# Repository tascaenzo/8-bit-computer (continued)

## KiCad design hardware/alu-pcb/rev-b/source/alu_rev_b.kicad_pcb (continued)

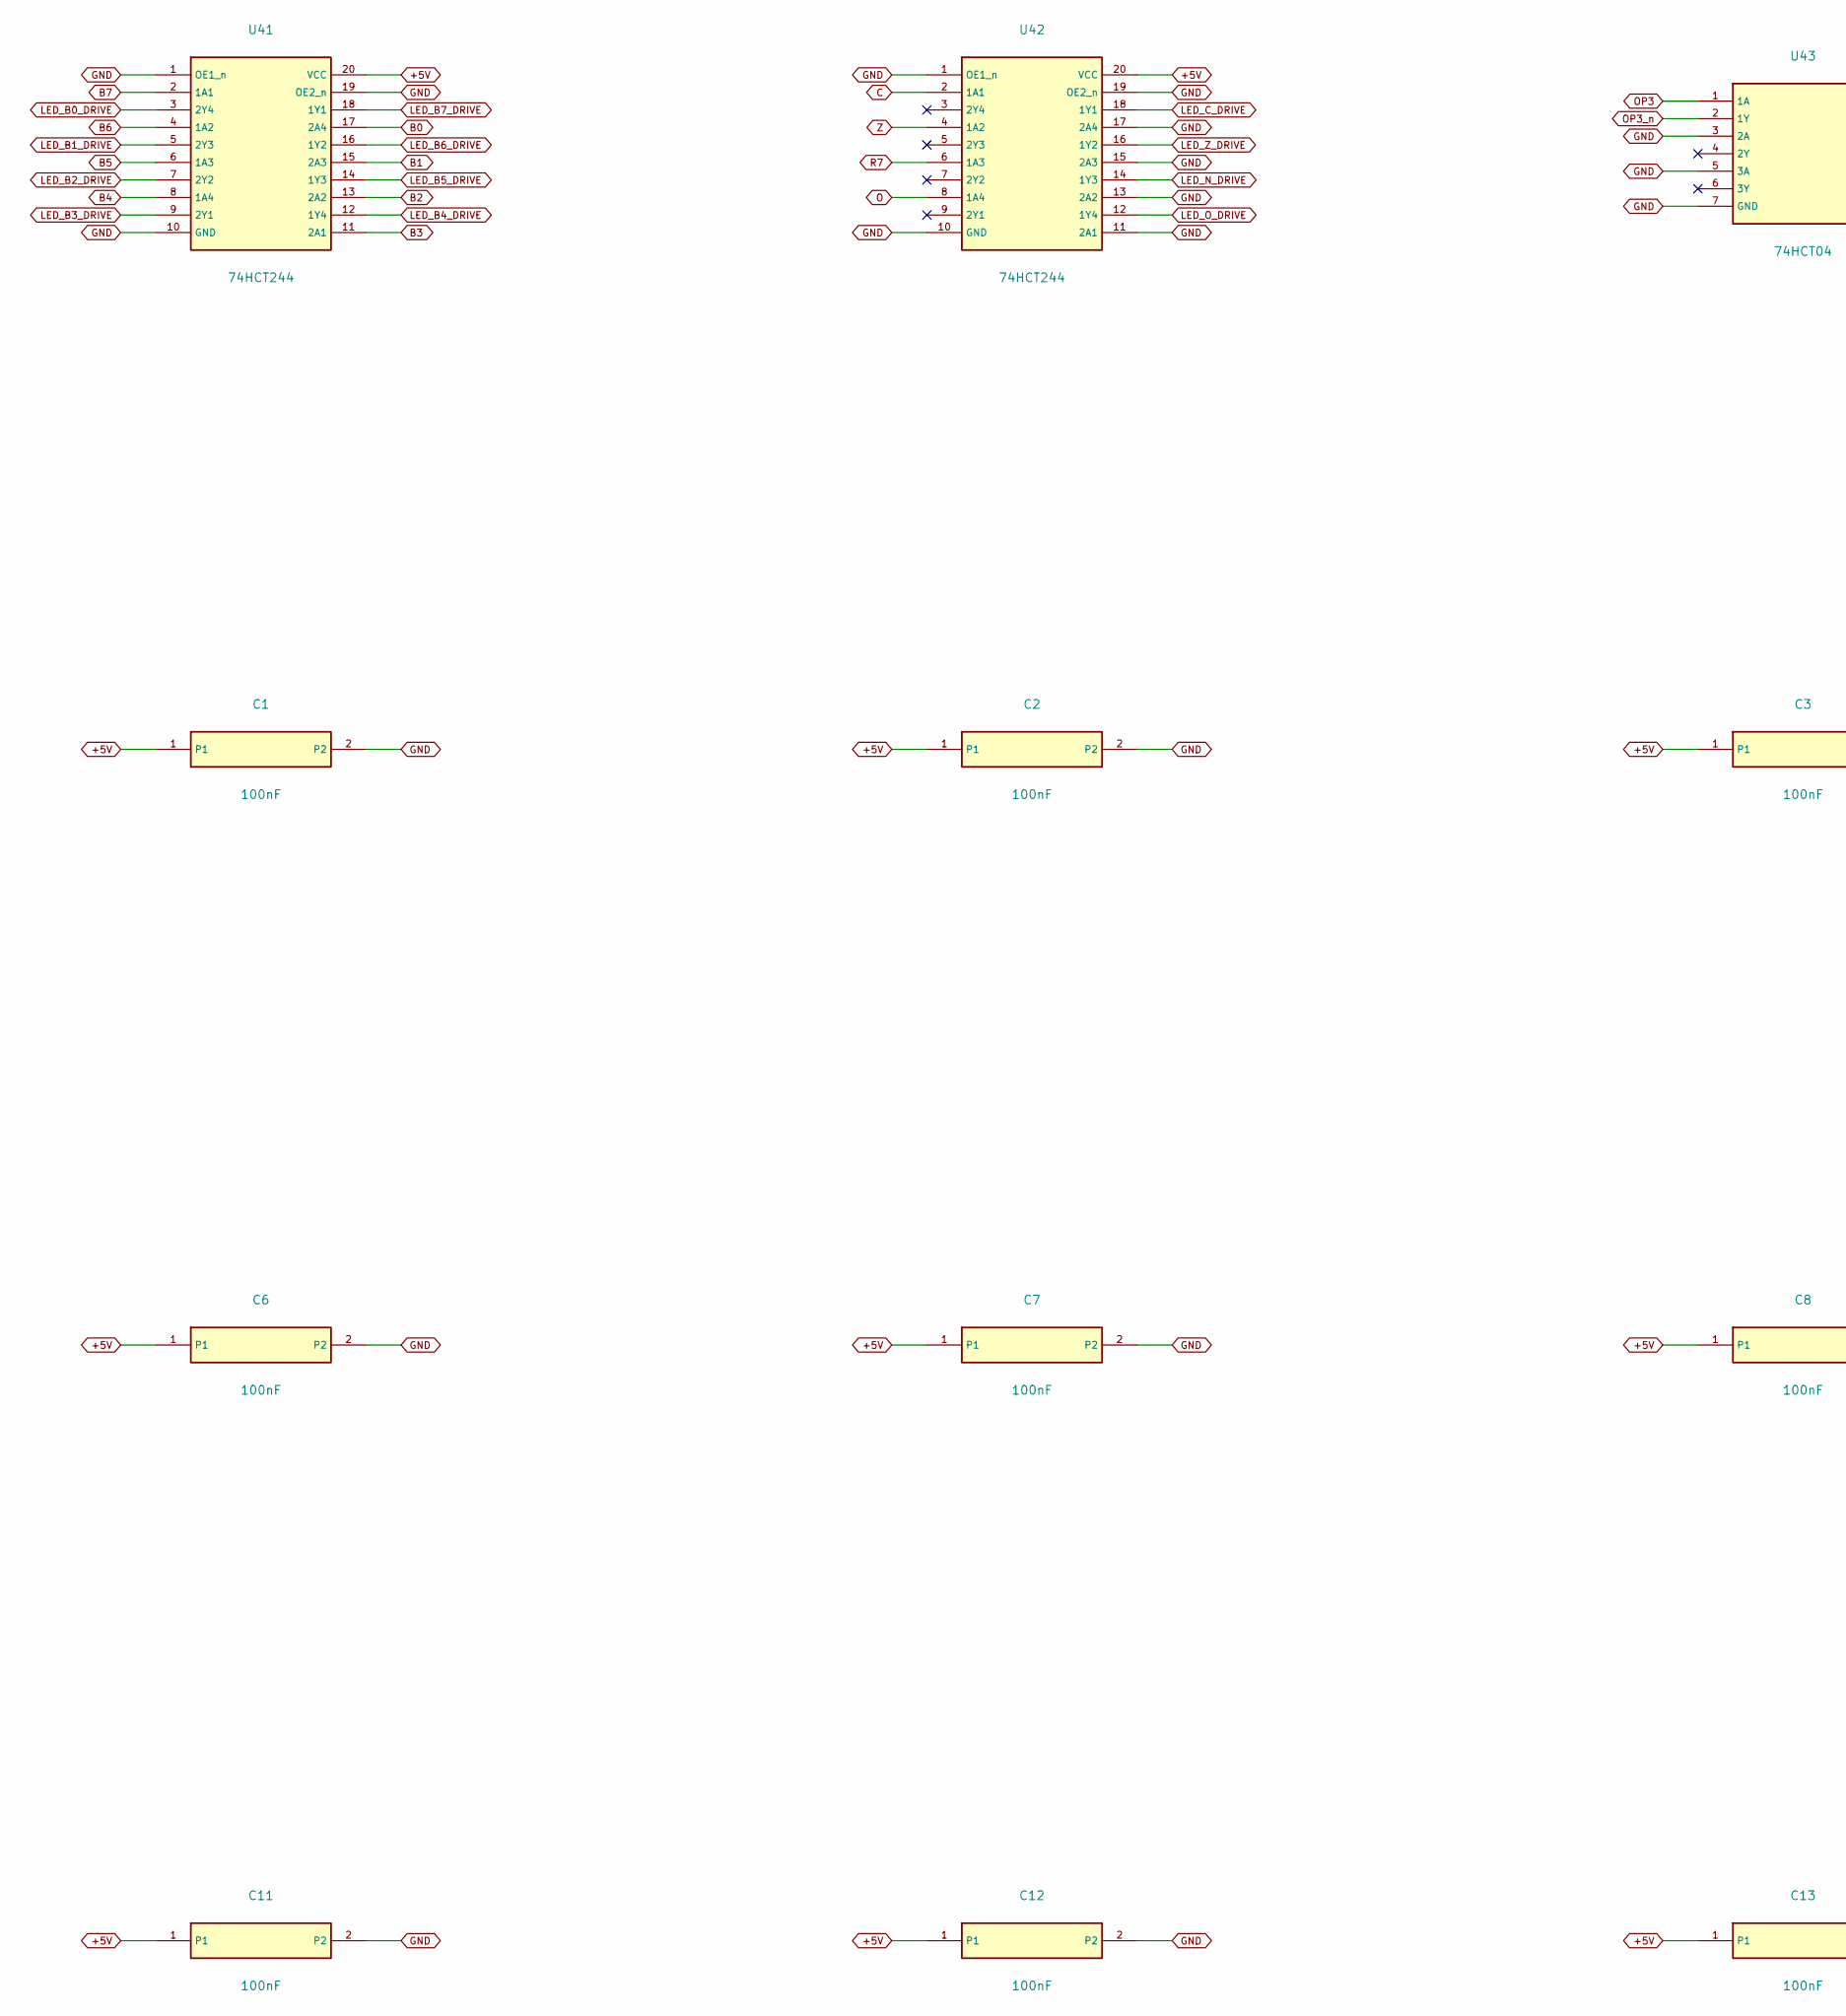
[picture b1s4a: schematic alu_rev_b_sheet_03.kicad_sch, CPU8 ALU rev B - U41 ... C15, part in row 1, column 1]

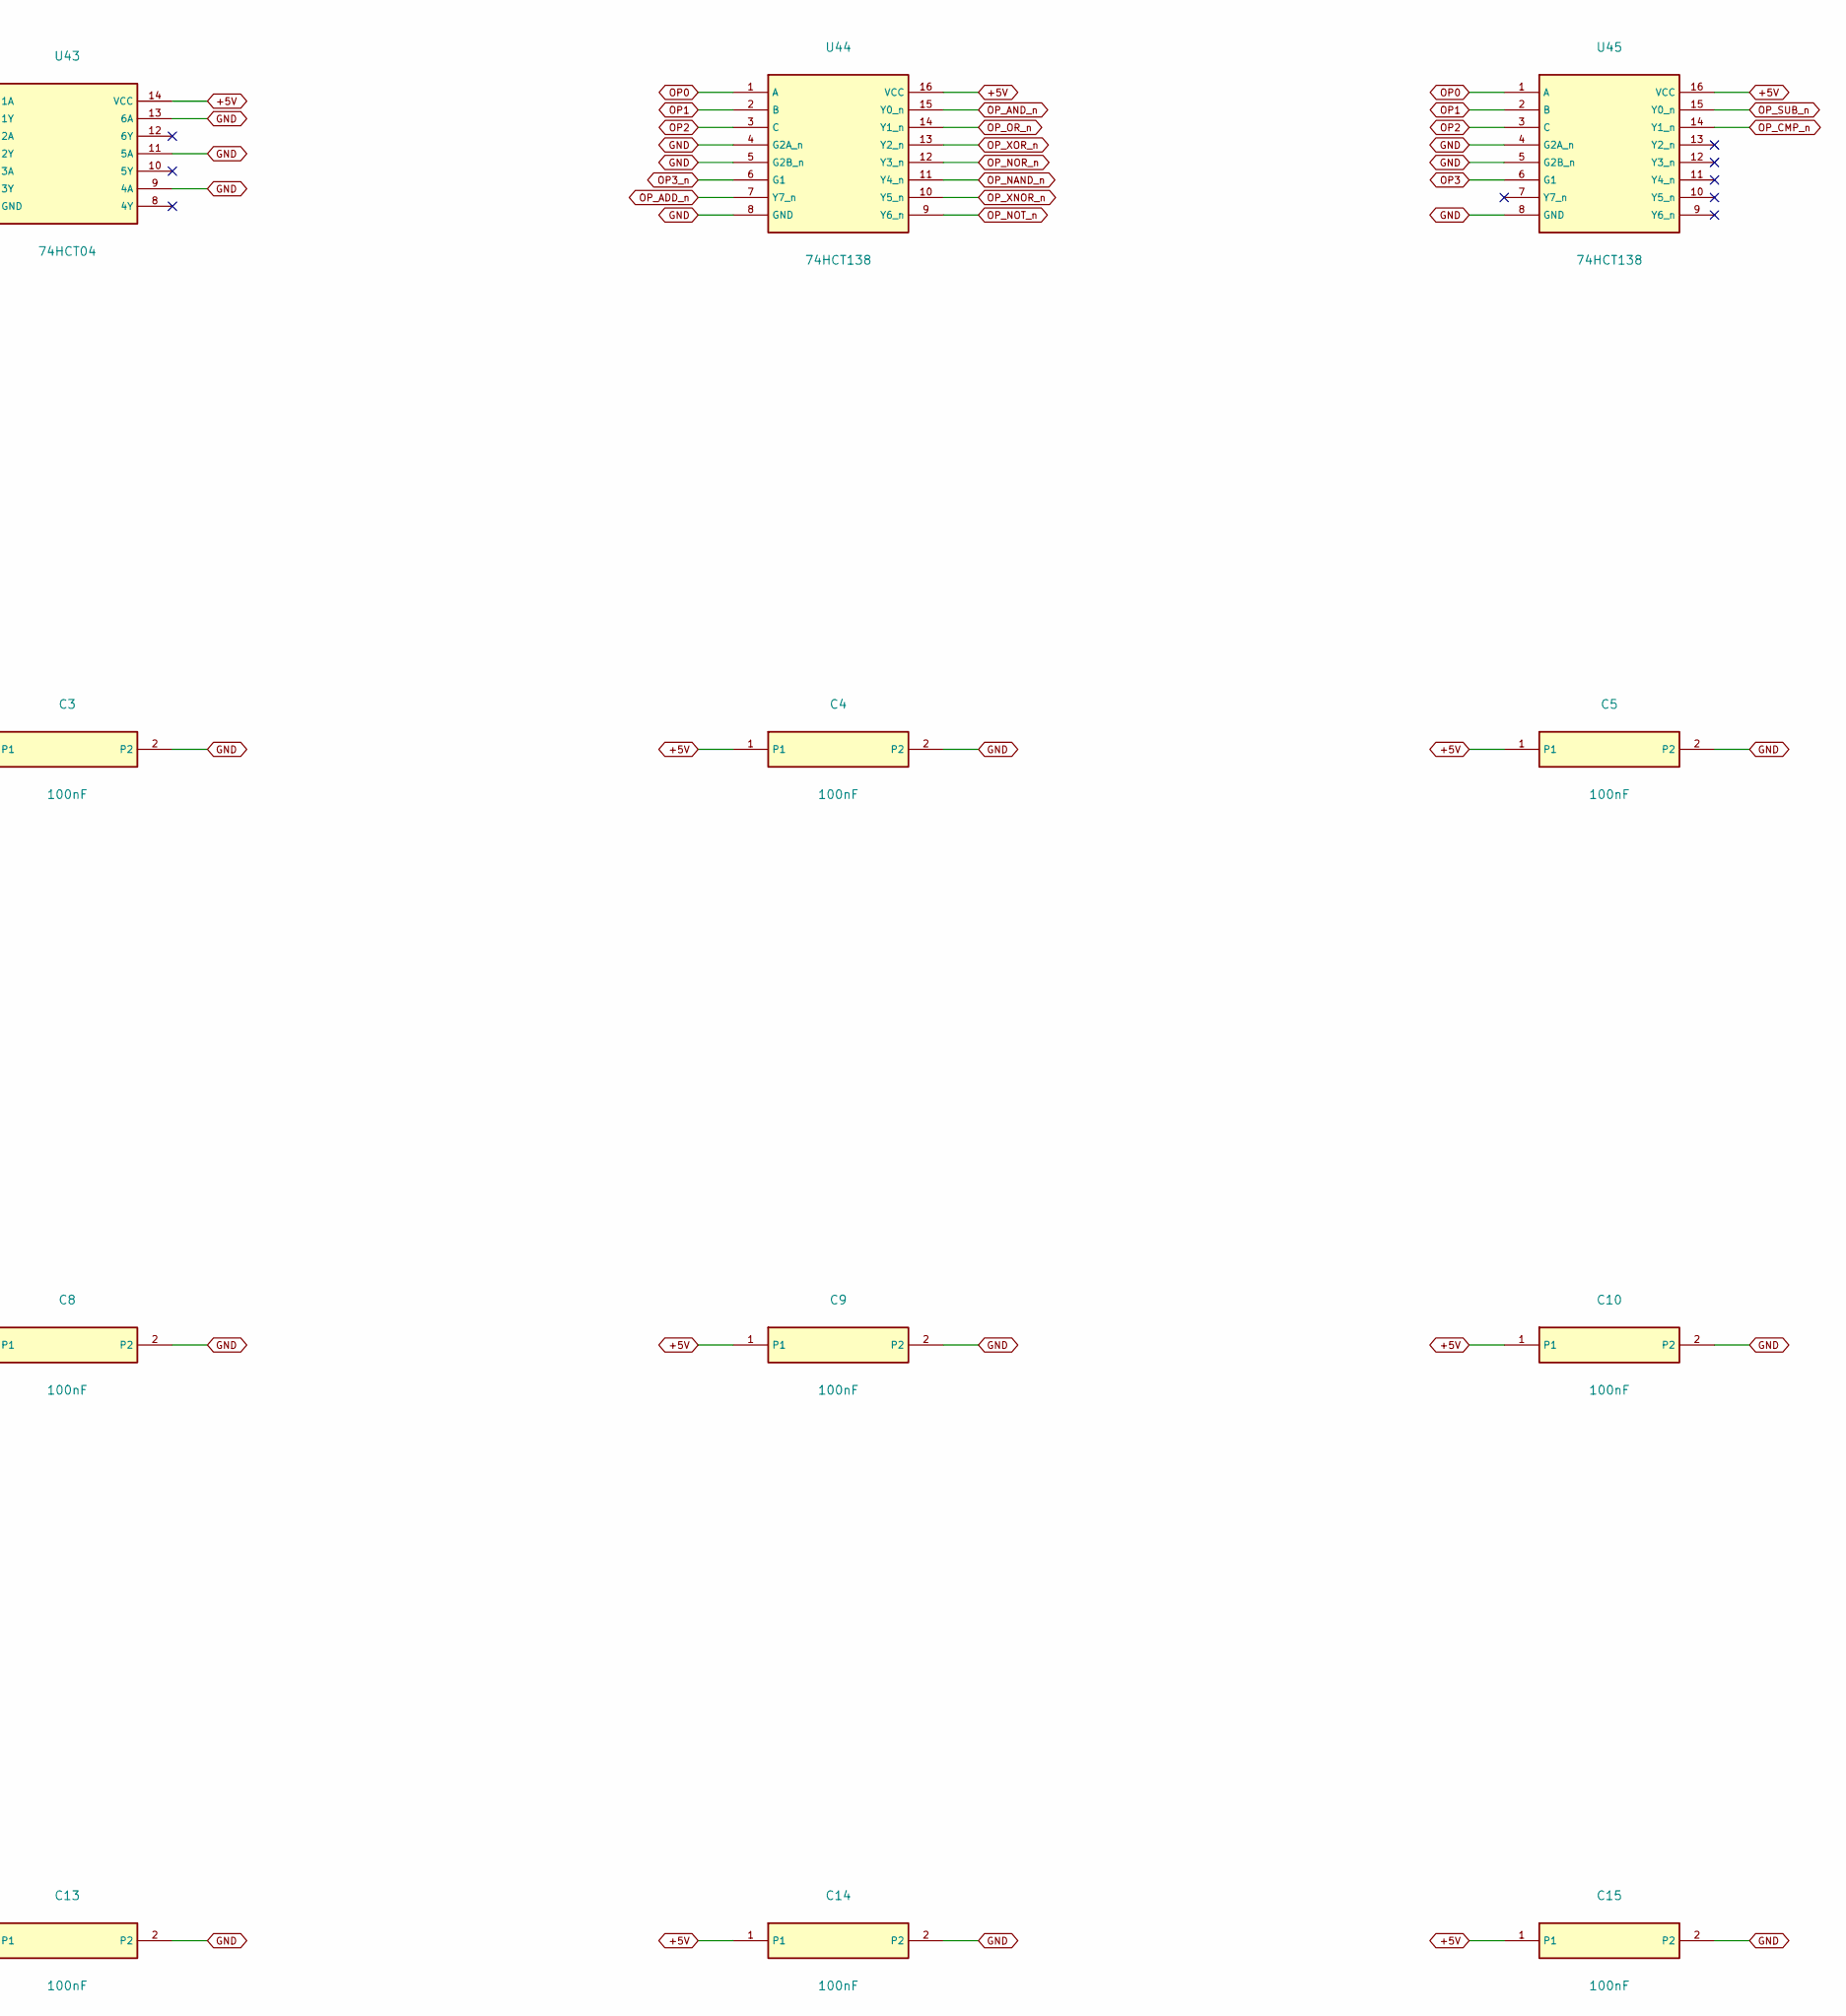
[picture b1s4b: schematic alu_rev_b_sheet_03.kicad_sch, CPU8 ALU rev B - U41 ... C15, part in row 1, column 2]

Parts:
C1, C2, C3, C4, C5, C6, C7, C8, C9, C10, C11, C12, C13, C14, C15: 100nF; C_Disc_P2.50mm
U41, U42: 74HCT244; DIP-20_W7.62mm
U43: 74HCT04; DIP-14_W7.62mm
U44, U45: 74HCT138; DIP-16_W7.62mm

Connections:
+5V: C1.1, C2.1, C3.1, C4.1, C5.1, C6.1, C7.1, C8.1, C9.1, C10.1, C11.1, C12.1, C13.1, C14.1, C15.1, U41.20 (VCC), U42.20 (VCC), U43.14 (VCC), U44.16 (VCC), U45.16 (VCC); also elsewhere on the board
B0: U41.17 (2A4); also elsewhere on the board
B1: U41.15 (2A3); also elsewhere on the board
B2: U41.13 (2A2); also elsewhere on the board
B3: U41.11 (2A1); also elsewhere on the board
B4: U41.8 (1A4); also elsewhere on the board
B5: U41.6 (1A3); also elsewhere on the board
B6: U41.4 (1A2); also elsewhere on the board
B7: U41.2 (1A1); also elsewhere on the board
C: U42.2 (1A1); also elsewhere on the board
GND: C1.2, C2.2, C3.2, C4.2, C5.2, C6.2, C7.2, C8.2, C9.2, C10.2, C11.2, C12.2, C13.2, C14.2, C15.2, U41.1 (OE1_n), U41.10 (GND), U41.19 (OE2_n), U42.1 (OE1_n), U42.10 (GND), U42.11 (2A1), U42.13 (2A2), U42.15 (2A3), U42.17 (2A4), U42.19 (OE2_n), U43.3 (2A), U43.5 (3A), U43.7 (GND), U43.9 (4A), U43.11 (5A), U43.13 (6A), U44.4 (G2A_n), U44.5 (G2B_n), U44.8 (GND), U45.4 (G2A_n), U45.5 (G2B_n), U45.8 (GND); also elsewhere on the board
LED_B0_DRIVE: U41.3 (2Y4); also elsewhere on the board
LED_B1_DRIVE: U41.5 (2Y3); also elsewhere on the board
LED_B2_DRIVE: U41.7 (2Y2); also elsewhere on the board
LED_B3_DRIVE: U41.9 (2Y1); also elsewhere on the board
LED_B4_DRIVE: U41.12 (1Y4); also elsewhere on the board
LED_B5_DRIVE: U41.14 (1Y3); also elsewhere on the board
LED_B6_DRIVE: U41.16 (1Y2); also elsewhere on the board
LED_B7_DRIVE: U41.18 (1Y1); also elsewhere on the board
LED_C_DRIVE: U42.18 (1Y1); also elsewhere on the board
LED_N_DRIVE: U42.14 (1Y3); also elsewhere on the board
LED_O_DRIVE: U42.12 (1Y4); also elsewhere on the board
LED_Z_DRIVE: U42.16 (1Y2); also elsewhere on the board
O: U42.8 (1A4); also elsewhere on the board
OP0: U44.1 (A), U45.1 (A); also elsewhere on the board
OP1: U44.2 (B), U45.2 (B); also elsewhere on the board
OP2: U44.3 (C), U45.3 (C); also elsewhere on the board
OP3: U43.1 (1A), U45.6 (G1); also elsewhere on the board
OP3_n: U43.2 (1Y), U44.6 (G1)
OP_ADD_n: U44.7 (Y7_n); also elsewhere on the board
OP_AND_n: U44.15 (Y0_n); also elsewhere on the board
OP_CMP_n: U45.14 (Y1_n); also elsewhere on the board
OP_NAND_n: U44.11 (Y4_n); also elsewhere on the board
OP_NOR_n: U44.12 (Y3_n); also elsewhere on the board
OP_NOT_n: U44.9 (Y6_n); also elsewhere on the board
OP_OR_n: U44.14 (Y1_n); also elsewhere on the board
OP_SUB_n: U45.15 (Y0_n); also elsewhere on the board
OP_XNOR_n: U44.10 (Y5_n); also elsewhere on the board
OP_XOR_n: U44.13 (Y2_n); also elsewhere on the board
R7: U42.6 (1A3); also elsewhere on the board
Z: U42.4 (1A2); also elsewhere on the board

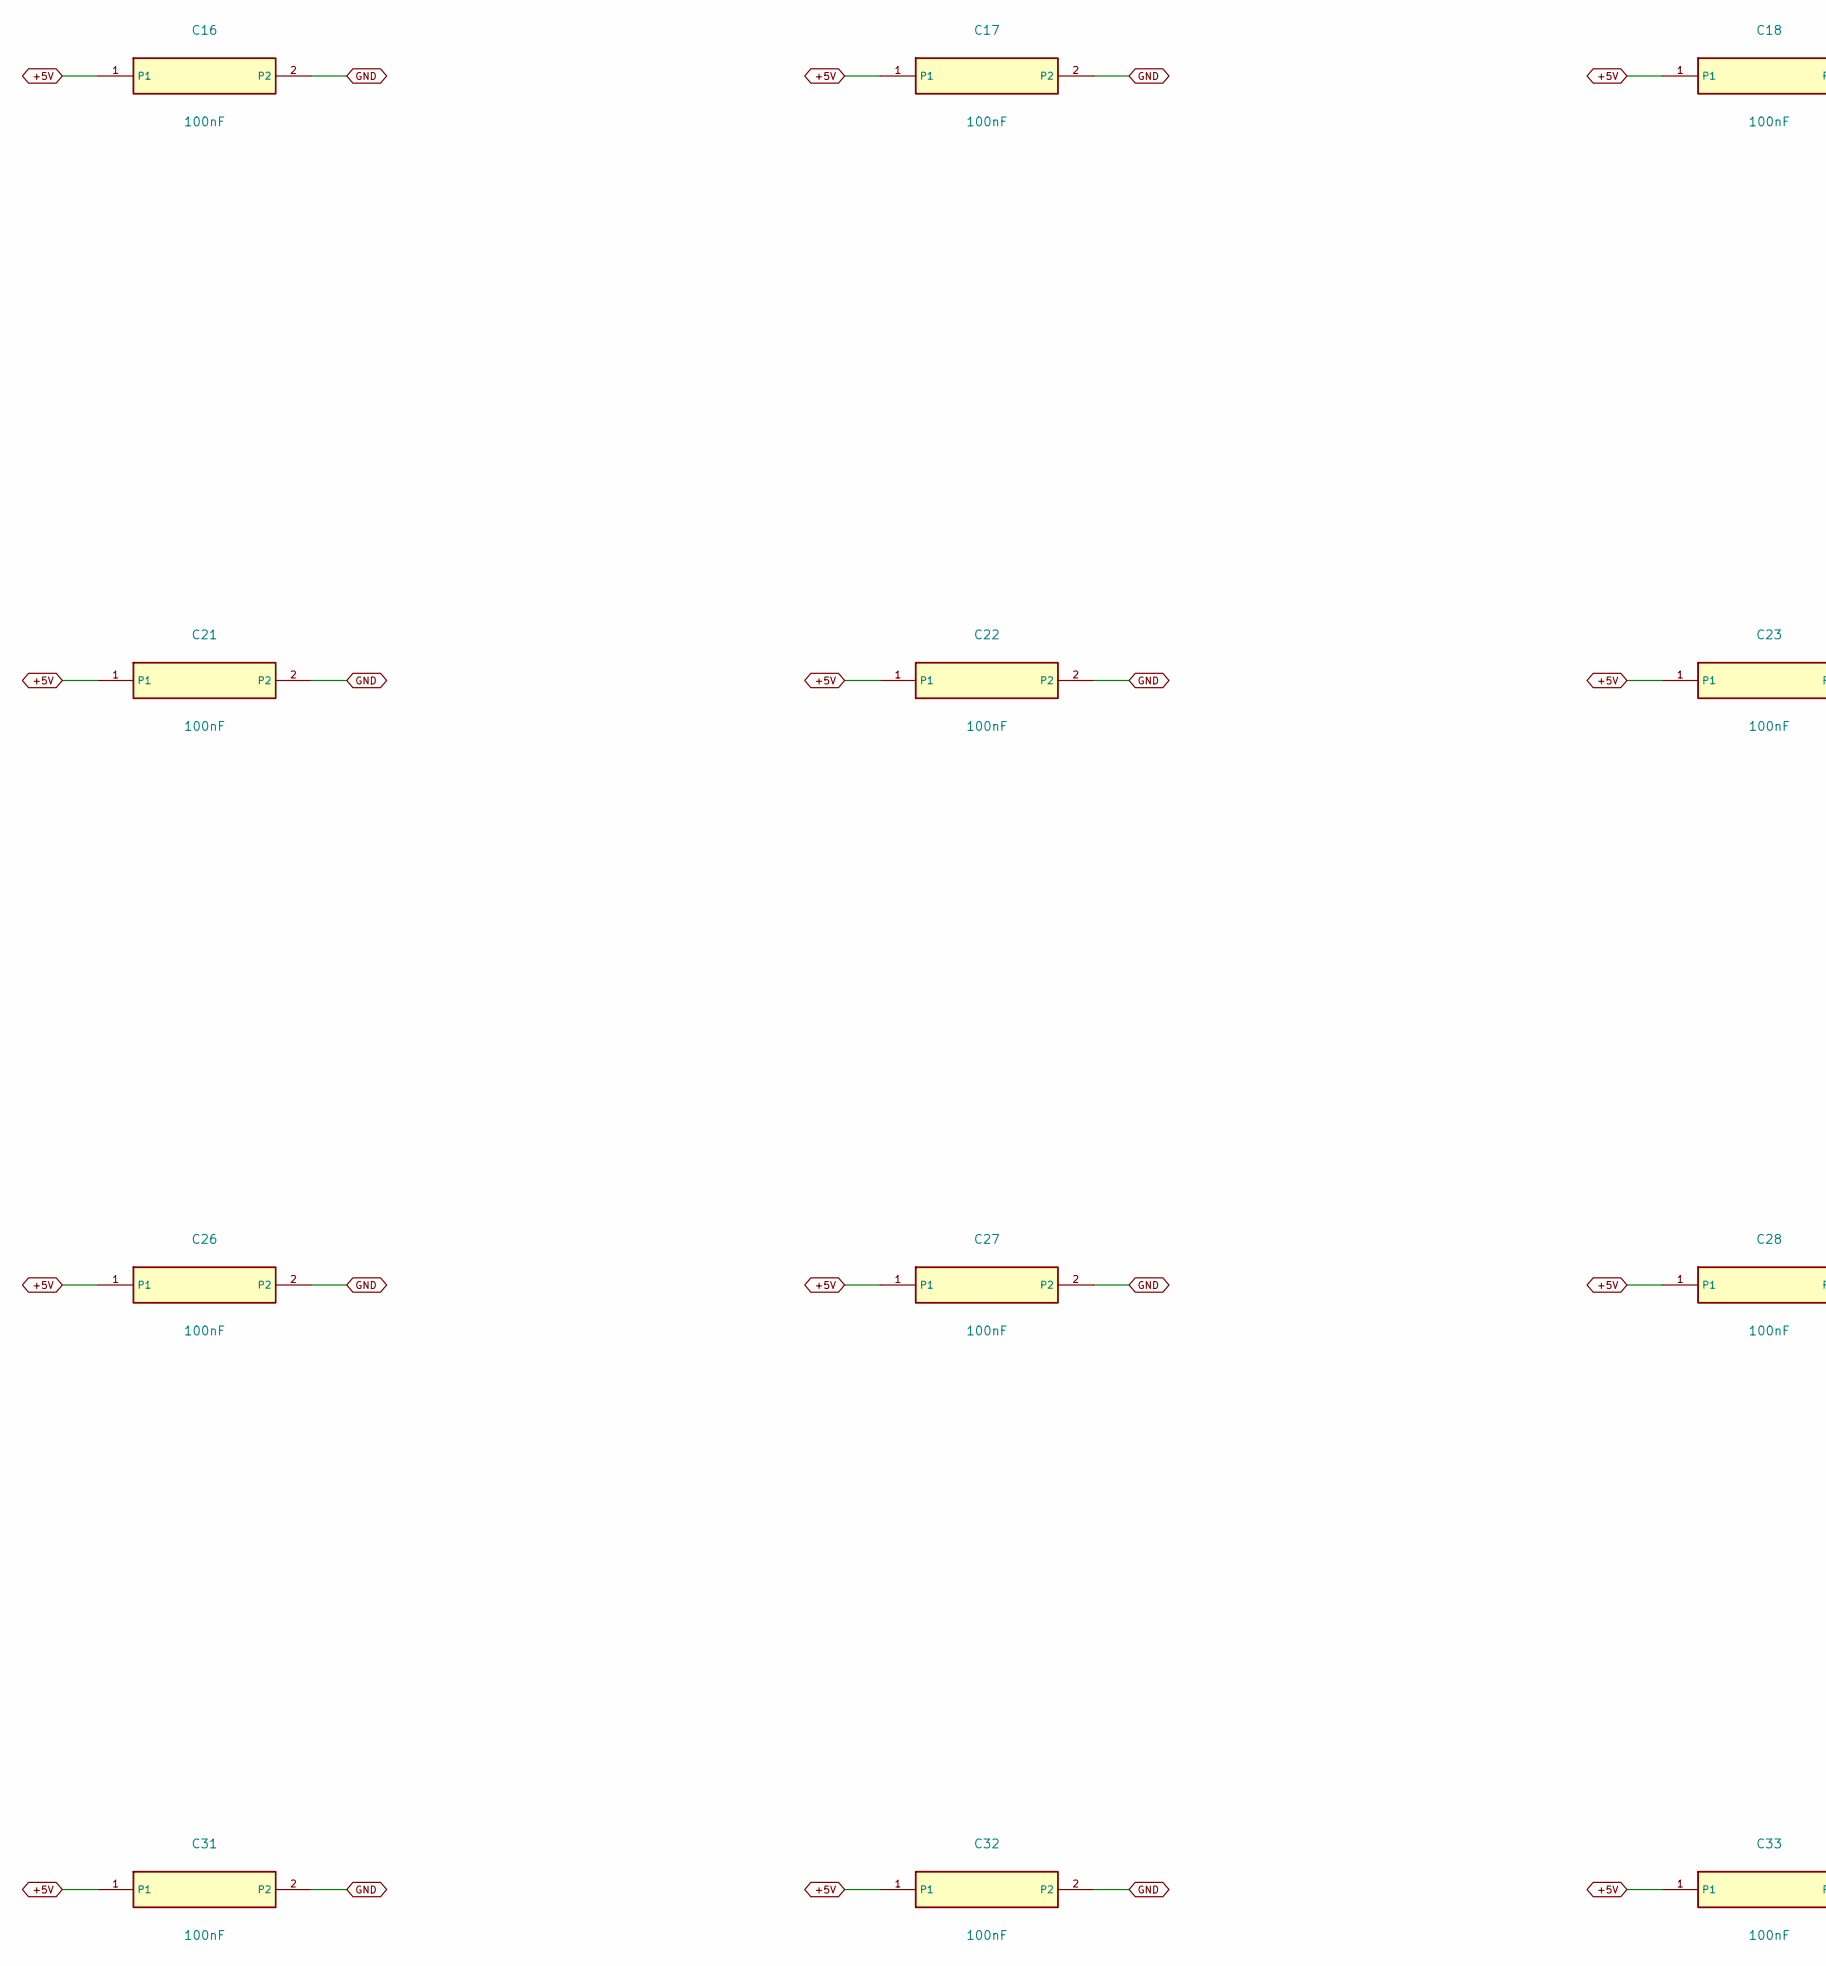
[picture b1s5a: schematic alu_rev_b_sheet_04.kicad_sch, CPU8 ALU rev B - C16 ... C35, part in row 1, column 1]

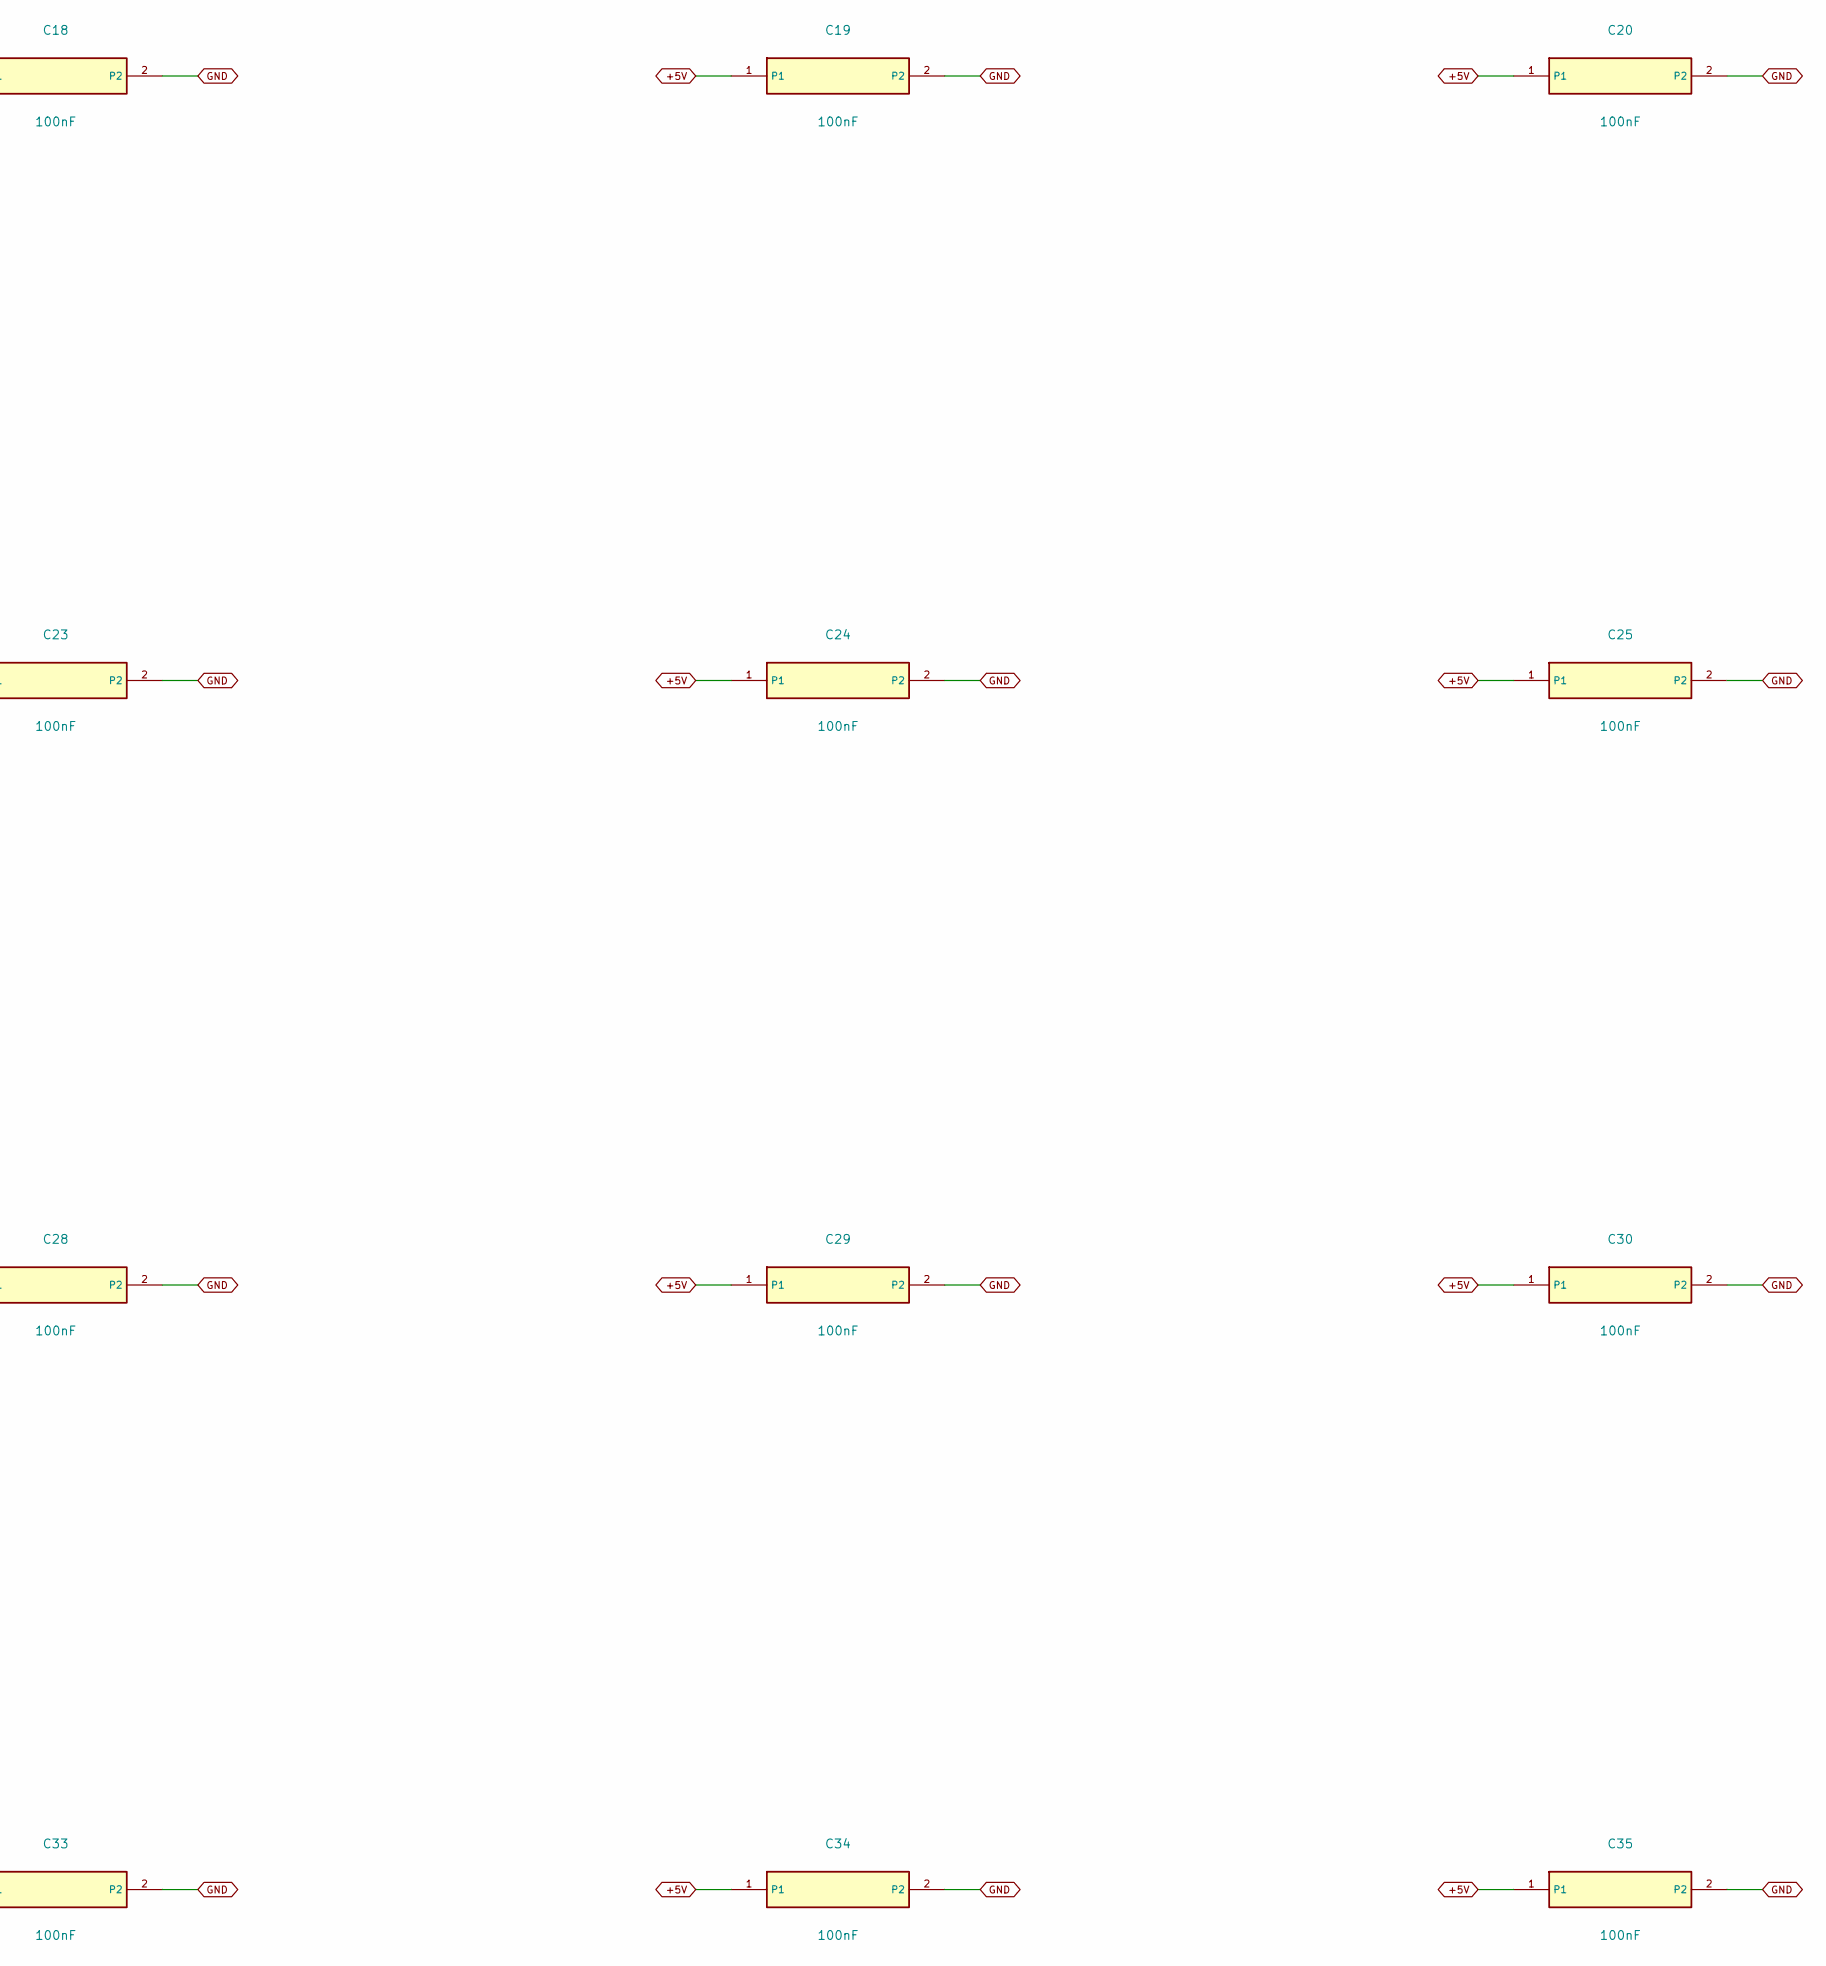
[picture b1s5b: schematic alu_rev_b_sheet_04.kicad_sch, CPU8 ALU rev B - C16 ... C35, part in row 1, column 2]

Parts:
C16, C17, C18, C19, C20, C21, C22, C23, C24, C25, C26, C27, C28, C29, C30, C31, C32, C33, C34, C35: 100nF; C_Disc_P2.50mm

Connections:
+5V: C16.1, C17.1, C18.1, C19.1, C20.1, C21.1, C22.1, C23.1, C24.1, C25.1, C26.1, C27.1, C28.1, C29.1, C30.1, C31.1, C32.1, C33.1, C34.1, C35.1; also elsewhere on the board
GND: C16.2, C17.2, C18.2, C19.2, C20.2, C21.2, C22.2, C23.2, C24.2, C25.2, C26.2, C27.2, C28.2, C29.2, C30.2, C31.2, C32.2, C33.2, C34.2, C35.2; also elsewhere on the board
